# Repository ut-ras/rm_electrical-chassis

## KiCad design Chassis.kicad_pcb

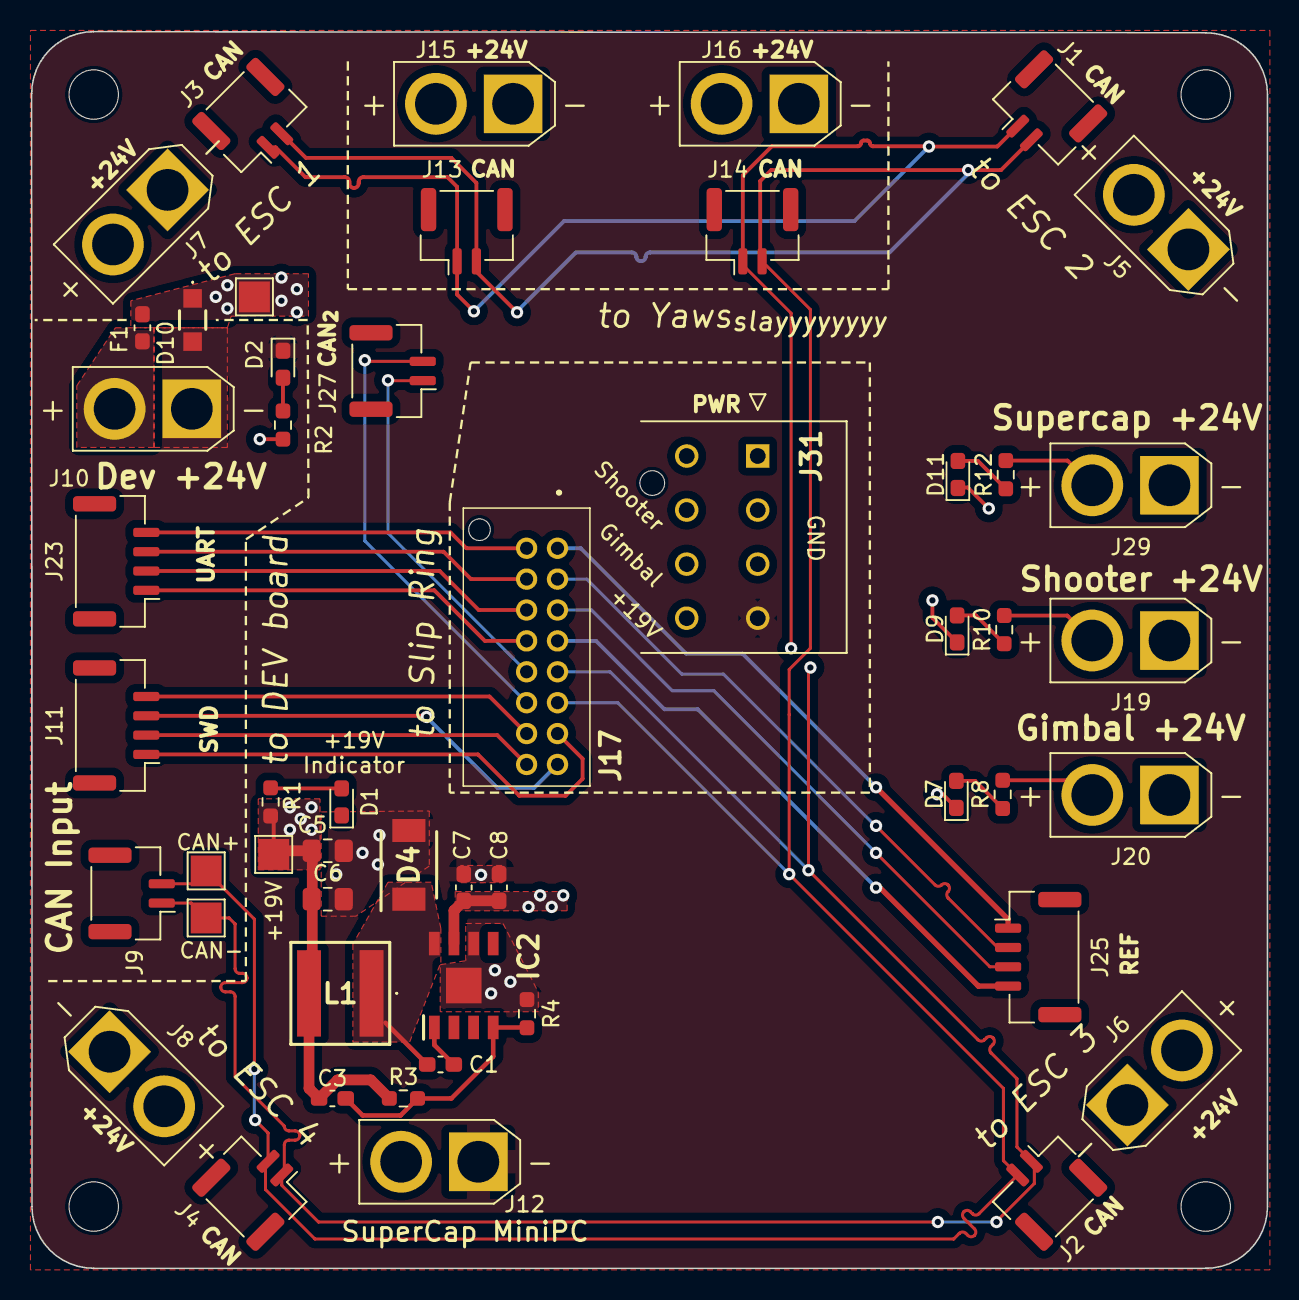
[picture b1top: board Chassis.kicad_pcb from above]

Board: 4 copper layers, 80.0 x 80.1 mm, 55 parts (0 on the bottom side), 34 nets.

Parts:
C1: 0.01u; C_0603_1608Metric_Pad1.08x0.95mm_HandSolder
C3: 82pF; C_0603_1608Metric_Pad1.08x0.95mm_HandSolder
C5, C6: 22µF; C_0805_2012Metric_Pad1.18x1.45mm_HandSolder
C7, C8: 4.7µF; C_0603_1608Metric_Pad1.08x0.95mm_HandSolder
D1: 150060BS75000; LED_0603_1608Metric_Pad1.05x0.95mm_HandSolder
D2: 150060RS75000; LED_0603_1608Metric_Pad1.05x0.95mm_HandSolder
D4: SR54F-AU_R2_000A1; SODFL5336X110N
D7, D9, D11: 150060YS75000; LED_0603_1608Metric_Pad1.05x0.95mm_HandSolder
D10: PTVS26VS1UR-QX; PTVS26VS1URQX
F1: 2.5A; Fuse_0603_1608Metric_Pad1.05x0.95mm_HandSolder
H1, H2, H3, H4: MountingHole; MountingHole_3.2mm_M3
IC2: RT6285GSP; SOIC127P600X175-9N
J1: FR_JST; JST_GH_BM02B-GHS-TBT_1x02-1MP_P1.25mm_Vertical
J2: BR_JST; JST_GH_BM02B-GHS-TBT_1x02-1MP_P1.25mm_Vertical
J3: FL_JST; JST_GH_BM02B-GHS-TBT_1x02-1MP_P1.25mm_Vertical
J4: BL_JST; JST_GH_BM02B-GHS-TBT_1x02-1MP_P1.25mm_Vertical
J5: FR_XT30; AMASS_XT30U-F_1x02_P5.0mm_Vertical
J6: BR_XT30; AMASS_XT30U-F_1x02_P5.0mm_Vertical
J7: FL_XT30; AMASS_XT30U-F_1x02_P5.0mm_Vertical
J8: BL_XT30; AMASS_XT30U-F_1x02_P5.0mm_Vertical
J9: IN_JST; JST_GH_BM02B-GHS-TBT_1x02-1MP_P1.25mm_Vertical
J10: IN_XT30; AMASS_XT30U-F_1x02_P5.0mm_Vertical
J11, J23, J25: Conn_01x04; JST_GH_BM04B-GHS-TBT_1x04-1MP_P1.25mm_Vertical
J12, J29: SUPCAP_XT30; AMASS_XT30U-F_1x02_P5.0mm_Vertical
J13: GIM1_JST; JST_GH_BM02B-GHS-TBT_1x02-1MP_P1.25mm_Vertical
J14: GIM2_JST; JST_GH_BM02B-GHS-TBT_1x02-1MP_P1.25mm_Vertical
J15: GIM1_XT30; AMASS_XT30U-F_1x02_P5.0mm_Vertical
J16: GIM2_XT30; AMASS_XT30U-F_1x02_P5.0mm_Vertical
J17: 501645-1620; 5016451620
J19: SHOO_XT30; AMASS_XT30U-F_1x02_P5.0mm_Vertical
J20: GIM_XT30; AMASS_XT30U-F_1x02_P5.0mm_Vertical
J27: CAN2_IN; JST_GH_BM02B-GHS-TBT_1x02-1MP_P1.25mm_Vertical
J31: Conn_01x08; 172298-YY08
L1: 10µH; MPLAL6060100
R1, R2, R8, R10, R12: 1kΩ; R_0603_1608Metric_Pad0.98x0.95mm_HandSolder
R3: 100kΩ; R_0603_1608Metric_Pad0.98x0.95mm_HandSolder
R4: 6.8kΩ; R_0603_1608Metric_Pad0.98x0.95mm_HandSolder
TP1, TP2, TP3, TP4: TestPoint; TestPoint_Pad_2.0x2.0mm

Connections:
+3.3V: J11.4, J17.14
+3V3: J17.2, J23.4
+24V: C7.1, C8.1, D10.1 (K), F1.2, IC2.7 (VIN), R2.2, TP3.1
/24V -> 19V Buck Convertor/BOOT: C1.2, IC2.1 (BOOT)
/24V -> 19V Buck Convertor/FB_{19}: C3.2, IC2.4 (FB), R3.2, R4.1
/24V -> 19V Buck Convertor/SW_{19}: C1.1, D4.1 (K), IC2.8 (SW), L1.1
/+19V: C3.1, C5.1, C6.1, J31.8, L1.2, R1.1, R3.1, TP4.1
/CAN1+: J1.2, J2.2, J3.2, J4.2, J9.2, J13.2, J14.2, J17.11, TP2.1
/CAN1-: J1.1, J2.1, J3.1, J4.1, J9.1, J13.1, J14.1, J17.9, TP1.1
/CAN2+: J17.12, J27.2
/CAN2-: J17.10, J27.1
/Gimbal_{+24V}: J15.2, J16.2, J20.2, J31.7, R8.2
/Mini_PC: F1.1, J10.2, J12.2
/Ref_{CAN}+: J17.5, J25.3
/Ref_{CAN}-: J17.3, J25.2
/Ref_{PWR}: J17.7, J25.4
/SWD_{SWCLK}: J11.2, J17.16
/SWD_{SWDIO}: J11.3, J17.15
/Shooter_{+24V}: J19.2, J31.6, R10.2
/SuperCap_{+24V}: J5.2, J6.2, J7.2, J8.2, J29.2, R12.2
/UART_{RX}: J17.4, J23.3
/UART_{TX}: J17.6, J23.2
GND: C5.2, C6.2, C7.2, C8.2, D2.1 (K), D4.2 (A), D10.2 (A), IC2.6 (GND_1), IC2.9 (GND_2), J10.1, J12.1, J31.4, R4.2
GND_CHASSIS: D11.1 (K), J5.1, J6.1, J7.1, J8.1, J29.1
GND_DEBUG: J11.1, J17.13
GND_GIMBAL: D7.1 (K), J15.1, J16.1, J20.1, J31.3
GND_REF: J17.1, J25.1
GND_SHOOTER: D9.1 (K), J19.1, J31.2
GND_UART: J17.8, J23.1
unnamed: D1.2 (A), R1.2
unnamed: D2.2 (A), R2.1
unnamed: D7.2 (A), R8.1
unnamed: D9.2 (A), R10.1
unnamed: D11.2 (A), R12.1

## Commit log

2023-09-09 initial chassis setup
2023-09-15 Create a .gitignore for the Chassis project
2023-09-17 Added submodule for Kicad and set libraries
2023-09-22 Added all connectors + assigned footprints + created PCB file
    Starting layout now
2023-09-23 Change polarity of pins + add circular trace
2023-09-24 Routed CAN lines + made hole octagonal
    + differential pair skew fixed
    Dimensions may be subject to change, will have to redimension and reroute
2023-09-24 Fixed colinear traces
2023-09-24 Possible indicator method?
2023-09-29 Lakshay's method
    I disagree
2023-09-29 Change to MOSFET architecture
    Low-side switching ftw
2023-10-14 Added Resistor and LED footprints to schematic
2023-10-20 Edit test point placement
2023-10-22 Completed initial layout
    I'm going to get roasted over some of these choices
2023-10-22 Finalized board design
    I think
    Also added more 3D models and whatnot
2023-10-22 Rearrange parts
2023-10-22 Updated step file
2023-10-22 Add/update READMEs
2023-10-22 Update README.md
    Add picture + note
2023-10-22 Add big boy connector
2023-10-22 move around connector
    g'night
2023-10-27 Add power connector
    big boy
2023-10-27 Update .STEP file
2023-11-03 Add vias to reduce current loops
2023-11-03 Added mounting holes
2023-11-04 Added pour for output
    Will need to add +5V buck + data connector + new power connector
    AAAAAAAAAAAAAAAAAAAAAAA
2023-11-10 updated xt30 footprints
2023-11-11 Add box to schematic
2023-11-11 reset
2023-11-17 +5V buck
2023-11-18 Pass DRC
2023-11-18 Adjust silkscreen
2023-11-18 Bury 5V feedback line b/c it ugly
2023-11-18 Reposition
2023-11-18 Straightened some kinks
2023-11-18 Remove some silks
2023-11-18 Add random microfit connector
    For data outputs
2023-12-02 began adding traces :p
2023-12-19 Added test points + part number for diode
2023-12-20 attempted to wire buck converter
2024-01-04 Remove unnecessary holes + made some thermal vias into direct pours
2024-01-05 Clear PCB
    Rerouting hajimaruyo
2024-01-05 Started routing some things
    Got connectors in mostly where they should be + general 5V buck layout done
2024-01-06 Much more pleasant dimensions
2024-01-07 Lots of placements
    Big blocks done, time to shuffle them around until I'm happy + route them
    4-layer board in the future?
2024-01-16 Did minor routing
2024-01-20 added mnfr numbers
2024-01-20 Finished routing
    Turns out we don't need the +5V buck kek
2024-01-27 added gimble power & motor connectors
2024-01-27 some things
2024-02-01 Add .STEP file
2024-02-02 Resizing again :D
2024-02-03 made 80x80 & changed to 8 pin connector
2024-02-17 added power sources
2024-02-24 Moved stuff around
    yeah
2024-03-02 layout done need to do ref system
2024-03-06 added traces, need to update pcb from schematic
2024-03-06 finishing touches!
2024-03-06 Touched up everything
    Improved pours + thermal pads, better routing, trace length matching
2024-03-07 Cleaned up silkscreen
    Went ham ngl
    Also passes all DRC checks
2024-03-08 J12 silkscreen names
2024-03-09 Create new STEP files
2024-03-09 Update silkscreen + address Lakshay's concerns
2024-03-09 Revert "added mnfr numbers"
    This reverts commit 8ea924c3256d347090cdc96d8489cfb264c97c81.
2024-03-09 Add another pour
2024-03-18 Add watchdog subsheet
2024-03-18 Update libraries & changed footprints
2024-03-22 added can2
2024-03-22 Adjust thingamajigs
    2nd CAN, silkscreen
2024-03-22 Remove unnecessary silkscreen + generate IBOM
2024-03-22 Adj silk
2024-03-22 Add le pikja
2024-03-22 Add names to board
2024-03-22 BOMs away
2024-03-23 Add the Roblox face
2024-03-23 Change output filtering for the +19V to 0805 (Mouser doesn't have 0603)
2024-03-23 Update footprints + pass DRC
2024-03-23 Fix power protection + adj silk
2024-03-23 Replace inductor with larger
    Idk how much current it'll need + invalid inductor data for spreadsheet
2024-03-24 Update and generate IBOM
2024-03-24 Add Gerber files & .ZIP
2024-03-24 Rename "plots" to "gerbers"
2024-03-29 Add BOM (part 2)
2024-04-20 Update submodule + started assembly
2024-04-27 Assembled all passives
2024-11-11 Andrew added hierarchical labels to in/out pins on schematic
2024-11-15 added i2c and chassis power to supercap to schematic
2024-11-16 added connections for chassis power to supercap
2024-11-23 Added hierarchical labels to ground pins in chassis
2024-11-23 added supercap connection
2024-12-07 separated grounds of powers
2025-01-31 Prepped Chassis for final review
2025-01-31 Changed out floating ground connection to its proper counterpart
2025-02-03 Finalized Chassis Board
2025-02-07 add silkscreen labels
2025-02-21 Fixed hierachical labels for functionality, naming needs to be changed
2025-03-07 Added hierarchical outputs to chassis grounds
2025-03-20 New connector, TODO: resolve CAN routing
2025-03-21 Resolved CAN junction
2025-03-21 updated fab files to match CAN change
2025-03-21 Added library submodule, converted to 9.0
2025-03-22 Update library to checkout on submodule update
2025-03-22 Modified symbol table to point to local kicad lib submodule
2025-03-22 Update fp/sym tables
2025-03-25 Updated fab files
2025-03-25 Rename gerber zip file
2025-04-12 Regenerated gerbers to be correct to new iteration
2025-04-16 Add 10nF bootstrap cap
2025-04-19 started layout for dev board interface pcb
2025-04-22 Staging changes
2025-05-30 Replaced Chassis PWR conn w/ Supercap PWR
2025-05-30 Move pours around + fix any DRC issues
2026-01-23 Prepped for work
2026-06-06 Inventoried all parts available for 2nd chassis board
